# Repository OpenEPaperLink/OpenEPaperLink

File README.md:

# OpenEPaperLink

This is an alternative firmware and protocol for the multiple Electronic Shelf Labels. It can be used to set up E-Paper tags and supply them with content.

The software in this project consists of two parts: Accesspoint-firmware and Tag firmware.
Additionally, there are various hardware designs for accesspoints and flasher-interfaces to program the tags, preferably using programming jigs

>[!Note]
>Please refer to the [Wiki](https://github.com/jjwbruijn/OpenEPaperLink/wiki) for the latest information.
>
>Much of this README is now obsolete, but it has been retained for historical reference.
>
>For example the use of tags as RF coprocessors is no longer supported.
 
## Aims
- Low power (currently around 9µA with a minimum of 40 second latency)
- Even lower power when there's no AP around
- Low latency (tags can check for new data every 40 seconds)
- High transfer speeds - It can do about 5kbyte/s in favorable RF conditions. This allows for lower power
- RF-friendly - We don't need to acknowledge EVERY packet, and we don't need to transfer data we already have

## What is required to set up OpenEPaperLink

On the [Wiki](https://github.com/jjwbruijn/OpenEPaperLink/wiki) there is a ton of information regarding all kinds of tags and building the access points.

The entire setup requires a few tags and an ESP32. A tag is used as an 802.15.4 radio for the ESP32. You'll need a ZBS_Flasher in order to flash the tags. Using the 'mac' option on ZBS_Flasher makes sure a tag flashed with a custom firmware has a valid mac address; it uses the stock mac address assigned to the tag if it hasn't been flashed before. If you want to set it yourself, you can edit the mac address in the infopage.

You can hook the AP tag up to the ESP32 with mod wires or a flex PCB. The esp will flash the AP firmware to the Tag automatically. In some cases, a power off/on cycle is required. Please check the serial console output for status information.

After programming the ESP32, make sure to also program the filesystem. This will upload the 'data' folder to the ESP32, with the webinterface.

## OpenEPaperLink Parts and links
* [Mini AP](https://github.com/OpenEPaperLink/Hardware/tree/main/OpenEPaperLink%20Mini%20AP)
* [Combined Flasher and AP](https://github.com/OpenEPaperLink/Hardware/tree/main/OpenEPaperLink%20AP%20and%20Flasher)
* [ATC1441's ZBS flasher page](https://github.com/atc1441/ZBS_Flasher)
* [Tags specs](https://github.com/jjwbruijn/OpenEPaperLink/wiki#tags)
* [Tags troubleshooting](https://github.com/jjwbruijn/OpenEPaperLink/wiki/Troubleshooting-Tags)

## The protocol explained
- The tag checks in with the AP every 40+ seconds. Actual check-in interval is highly dependent on RF conditions, or if the AP tells the tag to delay the next check-in
- The AP holds a list with tag MACs that have pending transfers.
- If a tag checks in, the AP replies with either no data, or information about a pending transfer
- The tag checks if this information is already downloaded to EEPROM, or is already displayed. If this is the case, the transfer is immediately cancelled by issuing a 'transfer complete' packet to the AP.
- The tag then proceeds to request data in 'blocks' of 4096 bytes. The AP responds with an ACK on the request, and specifies how long it will take to gather the data. The tag sleeps until the AP will send the data
- The AP requests its block-buffer to be filled by the ESP32, specifying MD5 and blockID
- Datablock is sent by the AP, which will take about 42 packets for a full block. The tag will keep track of which blocks it has seen
- After a block has been received with missing parts, the tag will request the same block, with a bitmask of blocks that are missing
- The AP responds with the parts as requested by the tag. If there aren't too many blocks requested, the AP will fill the block with duplicate parts, to increase the chance of a successful transmission
- After a full block has been received, the tag will do a simple checksum over all received data. If the checksum matches, the 4K of data is stored in EEPROM storage for later use
- The tag will now either request the next block, or do a full re-request if the checksum failed
- If all blocks are received, the tag will send a 'transfer complete'. 
- The AP will report the completed transfer to the ESP32, and removes the pendingData for this transfer from the queue

## Known issues:
- Some tags work better as APs than others. Your range may suck. The boards on these tags are tiny and fragile. For instance, a dab of hot-glue on a board is enough to warp it pretty severely, and will damage the components that are soldered on there. Reportedly, segmented-display Solum tags work well. 

## Hints and excuses:
- There is no warranty whatsoever. Nothing. Not implied or otherwise suggested. This code isn't fit for anything. Please don't use this code to do nasty things.
- Do a ```make clean``` between buildings for different boards. It really helps!
- This repo builds on SDCC 4.2.0 for Linux. Different SDCC versions can behave VERY differently.  Source sdcc/setup.sh to setup build a local copy and use it for compiling.
- We are happy and honored to see your pull requests! But please, no code/indent style changes :)

## Credits
### Large parts of this repo are based on code written by, and wouldn't be possible without the hard work of:
- dmitry.gr
- atc1441

Hats off to these legends!
 
## Automated Builds
- After a PR gets merged to the main branch, the changed code will be compiled.
- On release, files are added to enable OTA

## License
[Creative Commons Attribution-NonCommercial-ShareAlike 4.0 International (CC BY-NC-SA 4.0)](https://creativecommons.org/licenses/by-nc-sa/4.0/)

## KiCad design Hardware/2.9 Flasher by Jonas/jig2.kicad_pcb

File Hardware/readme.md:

Files in this directory where moved to https://github.com/OpenEPaperLink/Hardware

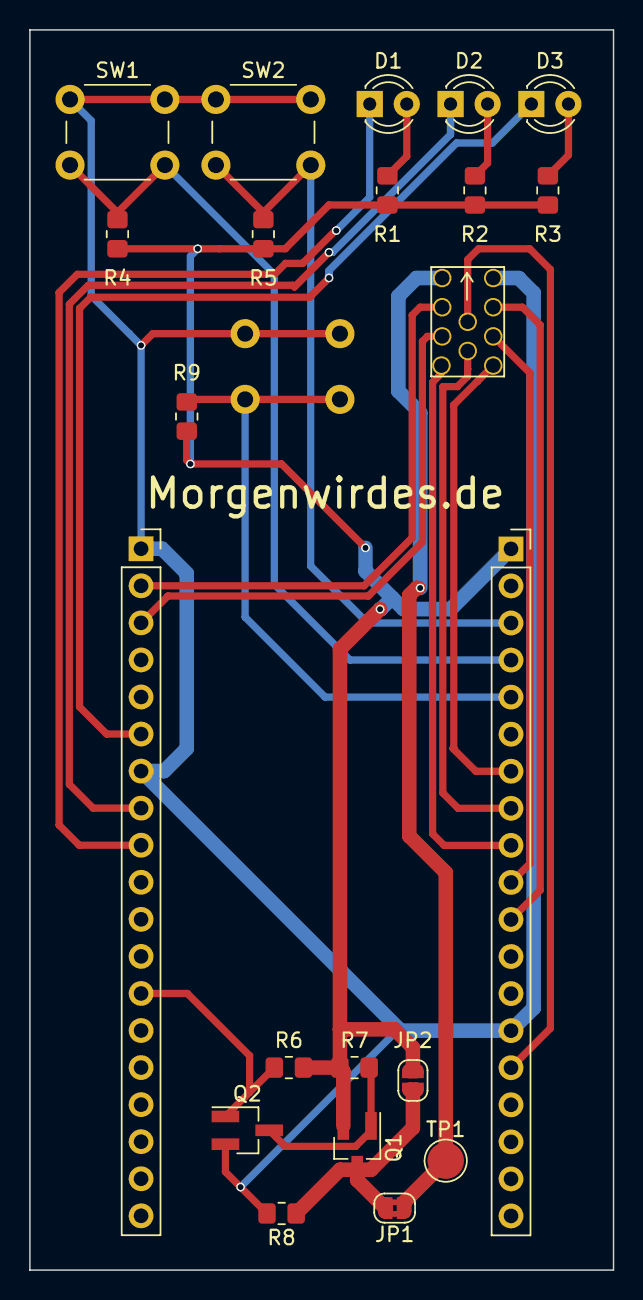
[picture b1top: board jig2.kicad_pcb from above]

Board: 2 copper layers, 40.0 x 85.0 mm, 23 parts (1 on the bottom side), 23 nets.

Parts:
D1: R; LED_D3.0mm
D2: Y; LED_D3.0mm
D3: G; LED_D3.0mm
J1: ESP32_Devkit_JL; PinSocket_1x19_P2.54mm_Vertical
J2: ESP32_Devkit_JR; PinSocket_1x19_P2.54mm_Vertical
JP1: SolderJumper_2_Bridged; SolderJumper-2_P1.3mm_Bridged2Bar_RoundedPad1.0x1.5mm
JP2: SolderJumper_2_Open; SolderJumper-2_P1.3mm_Open_RoundedPad1.0x1.5mm
Q1: Q_PMOS_GDS; SOT-23_Handsoldering
Q2: Q_NMOS_GSD; SOT-23_Handsoldering
R1, R2, R3: 1k; R_0805_2012Metric_Pad1.20x1.40mm_HandSolder
R4, R5, R6, R7, R8, R9: 10k; R_0805_2012Metric_Pad1.20x1.40mm_HandSolder
SW1, SW2, SW3: SW_Push; SW_PUSH_6mm
TP1: TestPoint; TestPoint_Pad_D2.5mm
U1: ESL-connector; SOLUM_ZBS_DEBUG

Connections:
+3.3V: J1.1, JP2.2 (B), Q1.2 (D), R1.2, R2.2, R3.2, R4.2, R5.2, R6.1, R7.1, R9.2
/ESL_P: JP1.2 (B), JP2.1 (A), Q1.3 (S), R8.1
/ESL_PWR: JP1.1 (A), TP1.1, U1.1 (VCC)
/GPI34: J1.5, R9.1, SW3.2
/GPI36: J1.3, R5.1, SW2.2
/GPI39: J1.4, R4.1, SW1.2
/GPIO4: J2.13, Q2.1 (G), R6.2
/GPIO13: J1.15, U1.5 (CLK)
/GPIO18: D1.1 (K), J2.9
/GPIO19: D2.1 (K), J2.8
/GPIO21: D3.1 (K), J2.6
/GPIO22: J2.3, U1.3 (SS)
/GPIO23: J2.2, U1.2 (MoSi)
/GPIO25: J1.9, U1.4 (TXD)
/GPIO26: J1.10, U1.9 (RXD)
/GPIO27: J1.11, U1.8 (RST)
/GPIO32: J1.7, U1.10 (P1.0)
/GPIO33: J1.8, U1.6 (MiSo)
GND: J1.14, J2.1, J2.7, Q2.2 (S), R8.2, SW1.1, SW2.1, SW3.1, U1.7 (GND)
unnamed: D1.2 (A), R1.1
unnamed: D2.2 (A), R2.1
unnamed: D3.2 (A), R3.1
unnamed: Q1.1 (G), Q2.3 (D), R7.2

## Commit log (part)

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2025-03-24 Avoid error message log print when parsers.json is missing
2025-03-24 Add Ethernet support
    The ethernet support allows to make the network/internet connection
    via LAN cable instead of WiFi. LAN is preferred, if a LAN cable is
    connected and a valid IP configuration via DHCP can be obtained, WiFi
    is switched off. If the LAN cable is disconnected, a fall back to
    WiFi is done.
    Use those defines in platform.ini for PHY settings:
2025-03-24 Add OpenEPaperLink_ESP32-PoE-ISO_AP to release build
2025-03-25 Added support for Elecrow C6 wireless module.
2025-03-25 Added optional (compile time) debug logging to C6 & H2.
2025-03-25 Added support for Elcrow Advanced 2.8" AP.
2025-03-25 Added E5.json for Elcrow Advanced 2.8" AP.
2025-03-26 Add new AP hardware support OpenEPaperLink_ESP32-PoE-ISO_AP (#431)
    * Fix filesystem mutex handling
    This fixes the re-initialization of the filesystem mutex when the dyn storage
    module is reinitialized. Using xSemaphoreCreateMutex would cause a memory leak
    when the begin function is called multiple times and a semaphore leakage could
    be caused by the re-initialization of the global fsMutex variable while the
    semaphore is taken.
2025-03-27 more robust extended sleep time and 'no updates between' handling
2025-03-27 stability improvements in C6 flashing
2025-03-28 OTA update tweaks
2025-03-31 Added 2.7" tagtype
2025-03-31 Delete resources/tagtypes/49.json
    47 already exists
2025-04-03 new tagtype M3 2.7" and M3 11.6" layouts and other tweaks
2025-04-05 fixes crash when dayahead data is unavailable
2025-04-05 Add OpenEPaperLink_Nano_TLSR_C6 and ESP32_S3_16_8_4inch_AP to automatic builds
2025-04-06 Added a Clock mode as content type
2025-04-12 added sunrise/sunset/moon phase to date display
2025-04-14 Added 5.81" BWR V2 because of UC Variant needs rotated image
2025-04-15 Enable zlib_compression support.
2025-04-27 css: fallback to 'monospace' for AP log view
    Log view on firmware update page was not printed using fixed width font on my system.
    Now it is.
    Closes: #460
2025-04-27 css: fallback to 'monospace' for AP log view (#461)
    Log view on firmware update page was not printed using fixed width font on my system.
    Now it is.
    Closes: #460
2025-05-18 Added more TagTypes
2025-05-19 Edited 800x480 Template
2025-05-26 Added more advanced Json template demo
2025-05-27 Create 29.json
    Added 2.4" BWRY definition
2025-05-29 TagType Update
2025-06-05 Added Chroma 74 BWR binaries version 0014.
2025-06-14 Button 3
2025-06-14 Button 3 (#473)
2025-06-14 fix build of serialap module
    wifimanager need to be used to read local IP address.
2025-06-14 fix build of serialap module (#475)
    wifimanager need to be used to read local IP address.
2025-07-06 Add configurable period for Google Calendar tags
2025-07-18 Chroma29 v0015: fix high battery current on some tags (#459).
2025-07-19 Updated Chroma29 entry in tagotaversions.json.
2025-07-20 Don't delay content generate when shorten latency is enabled and user is connected.
2025-08-01 Adding support for Waveshare ESP32-S3-ETH
2025-09-06 Ability to update time without requiring Internet Access
2025-09-11 Added DarkMode to AP Gui
2025-09-12 Also updated the .gz files
2025-09-15 Update painter.js
    Added more font sizes to support things like a single emoji on T-Panel and larger displays.
2025-09-15 Update main.js
    Adding support for cased versions of jpg and jpeg.
2025-10-17 New firmware hash found for ST-GR2900N.
2025-10-20 Feat: dayahead fixes and improvements
2025-10-20 Feat: dayahead fixes and improvements (#516)
2025-10-21 Add definitions for more now-known Solum BWRY tags
    https://github.com/OpenEPaperLink/Tag_FW_EFR32xG22/issues/11
2025-10-28 Add 11.6" BWRY and fix previous BWRY definitions
2025-10-30 Added BWRY Preview
2025-11-06 Added support for ts_option to provide finer control of time stamps. 1. Fixed time stamp overlap on weather forecast content on 2.9" tags. 2. Fixed time stamp overlap on AP info screen on 160x80 TFT 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
2025-11-16 Fixed the pin order for the display on the ESP32_S3_16_8_4inch_AP
2025-11-16 Updated the WebFiles as well
2025-11-20 Feature Wireguard Addon
2025-11-20 Feature Wireguard Addon remove README Files
2025-11-20 fix patch Wireguard-Library ciniml/WireGuard-ESP32@^0.1.5 add methode shutdown_timer_only
2025-11-23 Fix WireGuard crashes with automatic library patch
2025-11-23 Remove legancy File patch_wireguard.py
2025-12-06 Allow to disable sleep mode
2025-12-07 Use correct base templates for BWRY variants
2025-12-09 Updated UseGhz setting
2025-12-11 Added M3 2.6" BW
2025-12-16 Add a user authentication
2025-12-16 Add compressed www files
2026-01-18 Added V2 ATC_BLE_OEPL Advertising Handling
2026-01-24 Add SPAGHETTI for ESP32-S3 16MB Flash 8MB RAM
    same as yelllow AP but without TFT config.
2026-02-04 Create 006C.json
    This is for Hanshow Pro 154Q-N, 200x200 tested and working for me. The Hardware ID 0006C is what ATC_BLE_OEPL_Image_Upload tells me when i read Display Settings.
2026-02-04 Rename 006C.json to 006G.json
2026-02-04 Rename 006G.json to 06F.json
    Ok, 06G is not a valid Hex, is 06F ok?
2026-02-04 Rename 06F.json to 64.json
2026-02-13 Added 4F for 2.6" BWRY M3.
2026-02-13 Add definition for M3 4.2 BWRY
    https://github.com/OpenEPaperLink/Shared_OEPL_Definitions/pull/5
    https://github.com/OpenEPaperLink/Tag_FW_EFR32xG22/pull/16
2026-02-19 sunrise sunset moon phase fix
2026-02-20 add warning
2026-02-23 Added 91.json for the EL016F6W4A M3 1.6" BWRY variant.
2026-02-27 Added 2.9 and 2.13 High Res
2026-03-04 Created new AP setup using the Lilygo T-Display-S3 board (#423)
    * Created new AP setup using the Lilygo T-Display-S3 board
    * Updated UseGhz setting
2026-03-05 Point to Wiki for EFR32 tag flashing info from Tag Flasher readme.md.
2026-03-06 Missed erase function (#549)
    * Update swd.h
    * Update swd.cpp
    * Update usbflasher.cpp
2026-03-11 Enhance NTP configuration with DHCP support
    Added function to check if NTP servers are provided via DHCP.
2026-03-13 Fix buffer size truncation for non-8-aligned image dimensions
    Integer division (w*h)/8 truncates when w*h is not a multiple of 8,
    allocating one byte too few. spr2color then writes past the end of
    the buffer, corrupting the heap. Use (w*h+7)/8 to round up correctly.
    Triggered by any tag whose width*height is not divisible by 8.
2026-03-13 Fix buffer size truncation for non-8-aligned image dimensions (#561)
    Integer division (w*h)/8 truncates when w*h is not a multiple of 8,
    allocating one byte too few. spr2color then writes past the end of
    the buffer, corrupting the heap. Use (w*h+7)/8 to round up correctly.
    Triggered by any tag whose width*height is not divisible by 8.
2026-03-19 Better HD150 5.83" Design
2026-03-19 Better HD150 5,83" Content design
2026-03-30 Swap color values for black and white
2026-04-22 Add GICisky 2.9" BWRY display support
    The new 2.9" GICisky tag (model byte 0x2E) advertises on BLE and shows
    in the tag list but never updates, because OEPL only knew the 3-color
    BWR variants and sends image data as a dual bitplane. This display
    expects a single bitplane with 2 bpp packed pixels where 00=Black,
    01=White, 10=Yellow, 11=Red, per the hass-gicisky reference library.
    - Map manufacturer byte 0x2E to new GICI_BLE_EPD_29_BWRY (0xBC).
2026-04-26 + cron syntax for update interval
2026-05-07 Add Wolink/Zhsunyco BLE ESL 2.13" BWRY support
    Adds an entirely new BLE ESL family alongside the existing GICisky and
    ATC paths. The 2.13" BWRY tag advertises with manufacturer ID 0xAABB
    and uses a Wolink/Zhsunyco protocol over BLE only:
    - 16-byte AES-128-CBC challenge/response auth (zero IV, PKCS#7 pad)
    - 238 B chunked image upload with 4 B little-endian offset header
    - Single-bitplane 2 bpp pixel layout, column-major, y-flipped
2026-05-28 WIP - image generation working with hard coded test data.
2026-06-01 Honor LED off setting for yellow AP activity pulse
    On `HAS_TFT` boards the radio activity pulse was hardcoded to full
    brightness, ignoring a configured-off LED. Gate it on `maxledbrightness`
    so brightness 0 keeps the LED dark while non-zero still pulses at full.
2026-06-01 Honor LED off setting for C6 radio activity LED
    The C6 co-processor pulses its own GPIO activity LED on radio traffic,
    independent of the host's `config.led`. Carry the LED on/off state in a
    new `flags` byte of the `espSetChannelPower` (`SCP>`) command so the C6
    silences it when the LED is disabled, and re-send `SCP>` on a LED-only
    config change so it applies without a reboot.
    The struct gains a byte, so the host and C6 firmware are now version
2026-06-01 Add compile.sh shell port of compile.ps1
2026-06-05 WIP - image generation working with hard coded data for 400x300, 640x385 and 800x480 with actual battery, temperature and RSSI values from tag.
2026-06-06 WIP working end to end with live data. 1. Replaced TestOWM.cpp with OwmWeather.cpp. 2. Added support for entering Owm API config to web gui.
2026-06-08 Fix crash when timestamps are enabled and LOAD_GFXFF is defined.
2026-06-13 Add virtual (simulated) tags for hardware-free testing
    Create virtual (simulated) tags in the web UI to develop and test the AP
    without physical e-paper hardware. A virtual tag reuses the real
    processDataReq / sendDataAvail pipeline, so the AP behaves and broadcasts
    (e.g. wakeupReason over /ws) exactly as it would for a real tag.
    - new module src/virtualtag.{cpp,h} and a persisted isVirtual flag on tagRecord
    - endpoints POST /vtag_create and /vtag_event, plus wsSendVirtualLed for the
2026-06-15 add support for Gicisky BWRY 2.9" ESL
2026-06-20 Persist virtual tag immediately on creation
    The periodic saveDB() only runs every few minutes, so a virtual tag
    created via /vtag_create was lost if the AP restarted or was power-cycled
    before the next periodic save. Save the tag DB right after creating it,
    matching how the other web tag operations persist their changes.
2026-06-22 Added better CC1310M3 Firmware SubGhz
2026-06-23 Added better CC1310M2 Firmware SubGhz
